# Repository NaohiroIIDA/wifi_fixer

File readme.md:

# wifi_fixer_esp8266

## What is this?
"wifi_fixer" is an ESP8266 board for changing the Wifi-setting of Raspberry Pi from the outside using a smartphone.

## How does it work?
Wifi_fixer acts as an independent wifi access point. 
When you connect to this, the module show this by web browser. 
Enter the SSID / PASS of the external access point through this menu.

Raspberry Pi connect by  "/dev/serial0" (PIN:Tx RX)

### wifi_fixer.py
- Check Wifi is available
    - wifi_fixer module wait enter new SSID / PASS 
    - new SSID / PASS is entered, add to /etc/wpa_supplicant/wpa_supplicant.conf
    - Restart the raspberry pi

## Limits
--Only 2.4GHz wifi can be detected.
--If you have a large number of access points, you may not be able to find them.

## これは何？
ラズベリーパイのWifi設定を外部からスマートフォンを使って変更するためのESP8266ボード "wifi_fixer"です。

## どうやって動く？
Wifi_fixerは独立したwifiアクセスポイントとして動作します。スマートフォンでこのアクセスポイントに接続すると
内蔵したウェブサーバーを使ってメニューを表示します。このメニューを通じて外部のアクセスポイントのSSID/PASSの入力を行います。
ラズベリーパイとはTx/RXピンを通じ、/dev/serial0　を使ってシリアル通信を行います。

### wifi_fixer.py 
- Wifiが使用可能か調べる
- wifi_fixer モジュールにシリアル通信で問い合わせを行い、SSID/PASSが入力されているか調べる
- 新しいSSID/PASSが入力されたら、/etc/wpa_supplicant/wpa_supplicant.conf に追記
- ラズベリーパイをリスタート

## 制限
- 検出できるのは2.4GHz wifiのみです。
- 多数のアクセスポイントがある場合、発見できないことがあります。

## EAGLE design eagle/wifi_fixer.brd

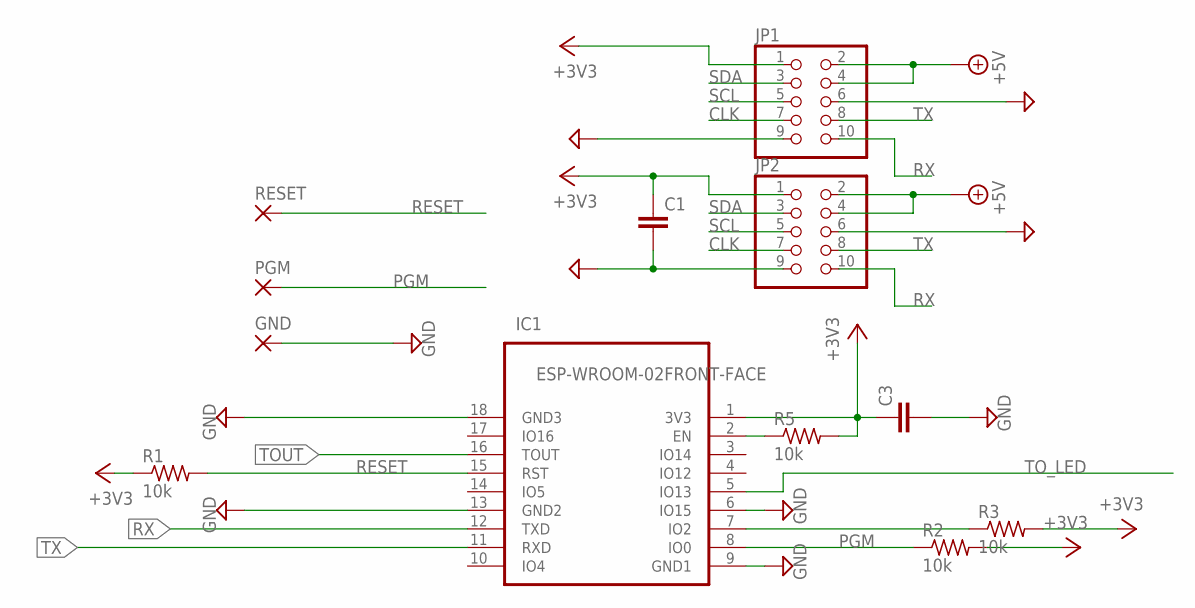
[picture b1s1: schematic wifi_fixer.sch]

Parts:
C1: C-EUC1206; C1206
C3: C-EUC0603; C0603
GND: SMD2; SMD1,27-2,54
IC1: ESP-WROOM-02FRONT-FACE; FRONT-FACE
JP1, JP2: PINHD-2X5; 2X05
PGM: SMD2; SMD1,27-2,54
R1, R2, R3, R5: 10k; R0603
RESET: SMD2; SMD1,27-2,54

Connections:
+3V3: C1.1, C3.1, IC1.1 (3V3), JP1.1, JP2.1, R1.1, R2.2, R3.2, R5.2
+5V: JP1.2, JP1.4, JP2.2, JP2.4
CLK: JP1.7, JP2.7
GND: C1.2, C3.2, GND.1, IC1.6 (IO15), IC1.9 (GND1), IC1.13 (GND2), IC1.18 (GND3), JP1.6, JP1.9, JP2.6, JP2.9
unnamed: IC1.7 (IO2), R3.1
unnamed: IC1.2 (EN), R5.1
PGM: IC1.8 (IO0), PGM.1, R2.1
RESET: IC1.15 (RST), R1.2, RESET.1
RX: IC1.12 (TXD), JP1.10, JP2.10
SCL: JP1.5, JP2.5
SDA: JP1.3, JP2.3
TOUT: IC1.16 (TOUT)
TO_LED: IC1.5 (IO13)
TX: IC1.11 (RXD), JP1.8, JP2.8

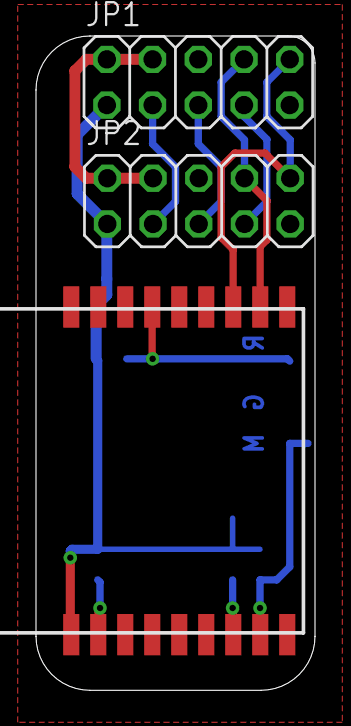
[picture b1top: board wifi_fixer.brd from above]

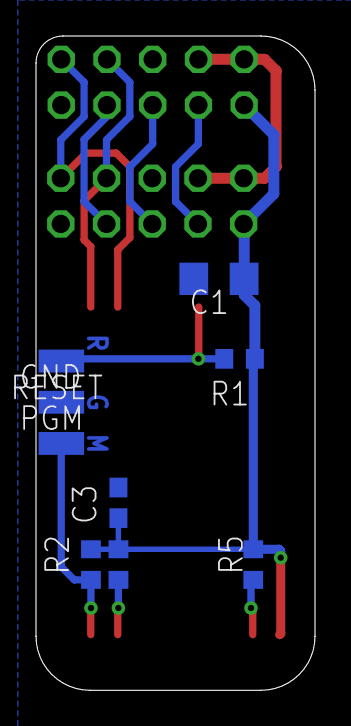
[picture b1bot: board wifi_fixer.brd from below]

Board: 2 copper layers, 15.5 x 36.4 mm, 12 parts (9 on the bottom side), 12 nets.

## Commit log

2021-04-30 fix1517
2021-04-30 fix1551
2021-04-30 fix1604
2021-04-30 ohno
